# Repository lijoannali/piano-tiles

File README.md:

# Piano Tiles 
A WS2812B LED array game written with "bare metal" C for the MSPM0G3507 for your simple entertainment needs...

## Demo Video

# Full-Length Project Presentation
[Link to Video](https://www.youtube.com/watch?v=sYHI2Lu6KRk)

# Team Members
- Cindy Nguyen
- Maha Razzaq
- Joanna Li
- Ivana Zak
  
# Project Report
[Link to Report](/report.pdf)

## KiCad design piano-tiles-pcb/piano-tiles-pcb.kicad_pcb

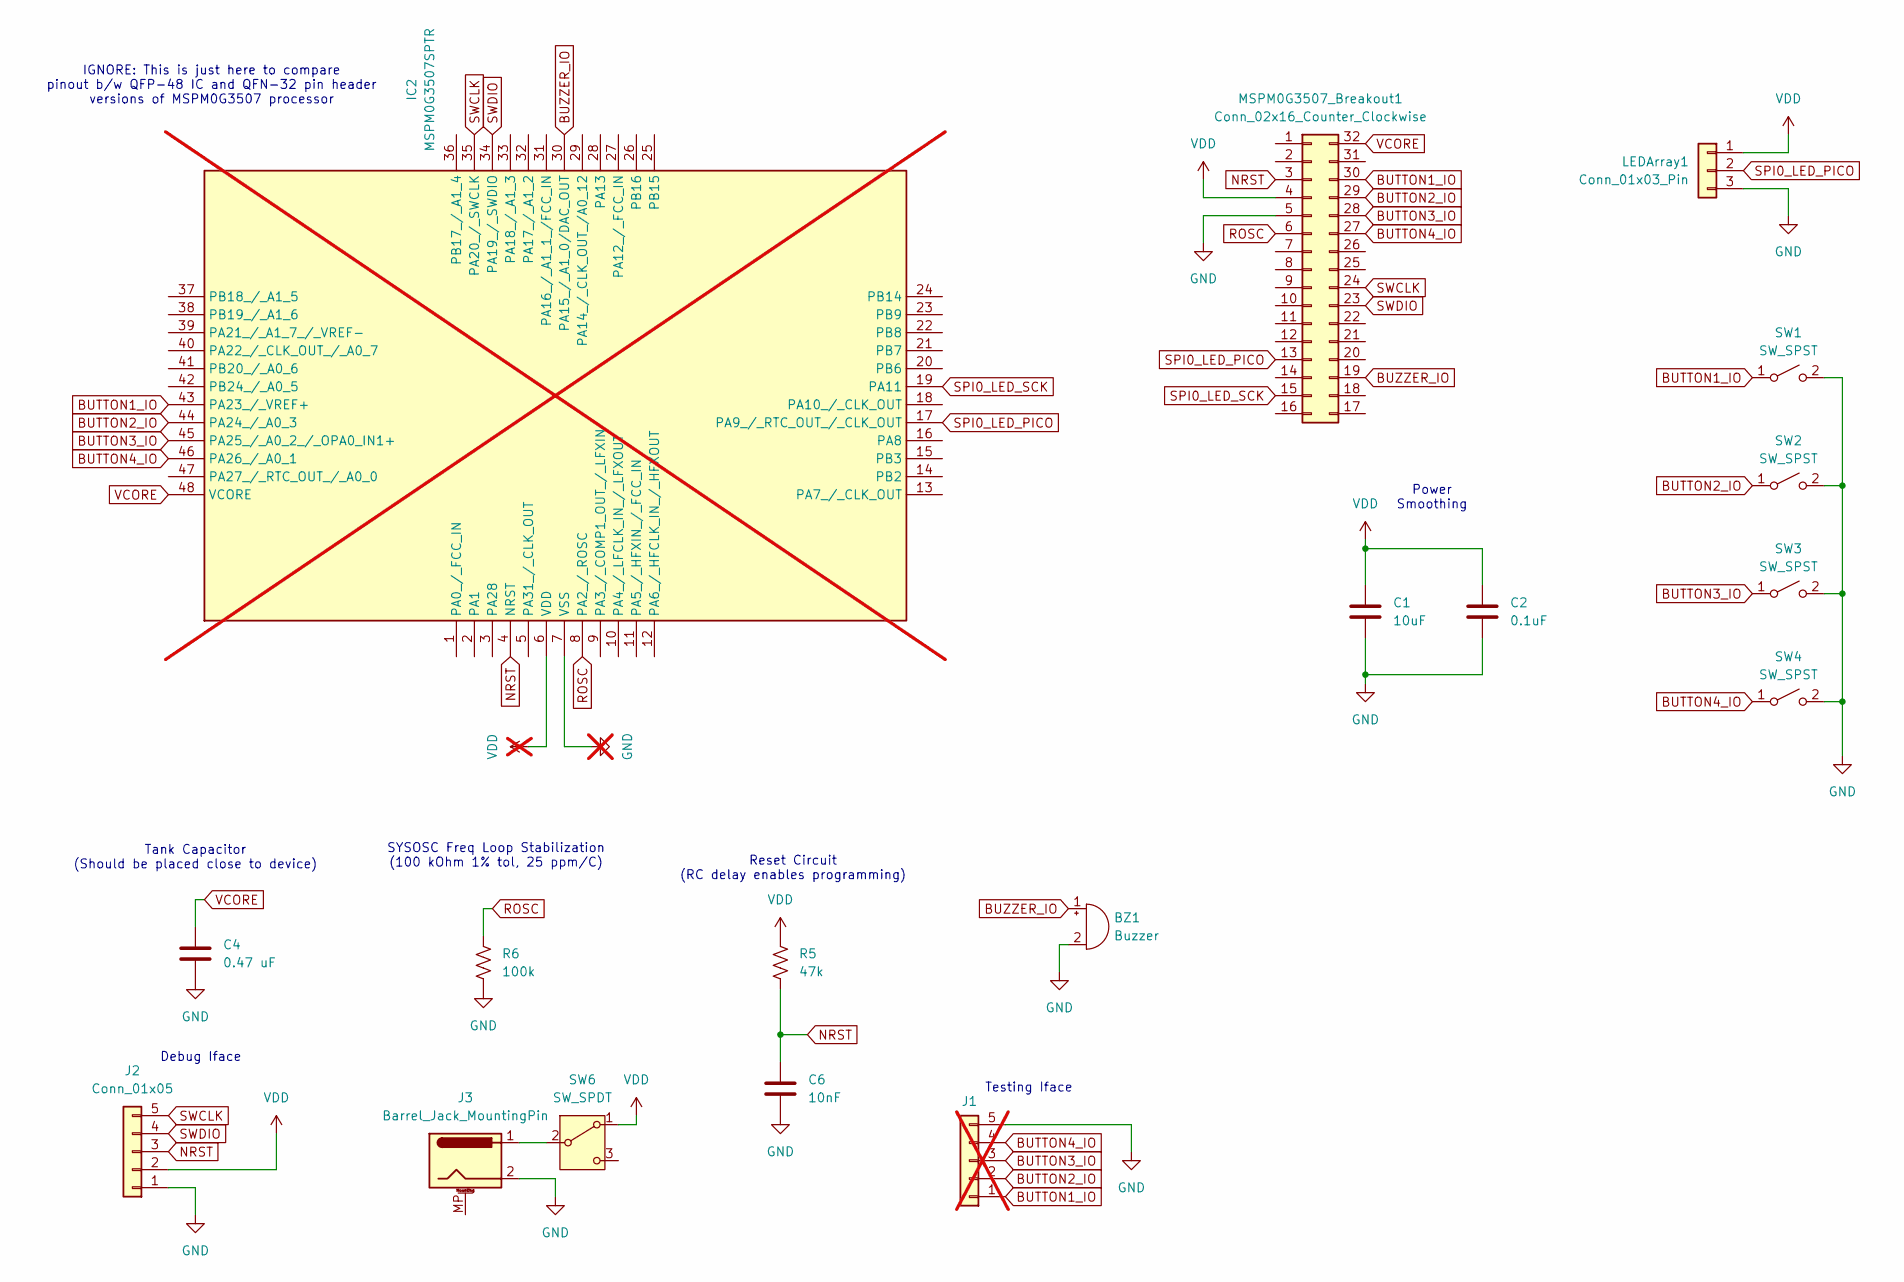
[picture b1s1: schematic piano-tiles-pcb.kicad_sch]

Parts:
BZ1: Buzzer; Buzzer_Murata_PKLCS1212E; LCSC Part # C113159
C1: 10uF; C_1206_3216Metric_Pad1.33x1.80mm_HandSolder
C2: 0.1uF; C_1206_3216Metric_Pad1.33x1.80mm_HandSolder
C4: 0.47 uF; C_1206_3216Metric_Pad1.33x1.80mm_HandSolder; LCSC Part # C13967
C6: 10nF; C_1206_3216Metric_Pad1.33x1.80mm_HandSolder; LCSC Part # C15195
IC2: MSPM0G3507SPTR; QFP50P900X900X160-48N; Mouser Part Number 595-MSPM0G3507SPTR; not fitted
J1: Conn_01x05; PinHeader_1x05_P2.54mm_Horizontal; not fitted
J2: Conn_01x05; PinHeader_1x05_P2.54mm_Horizontal; LCSC Part # C492413
J3: Barrel_Jack_MountingPin; BarrelJack_CUI_PJ-063AH_Horizontal
LEDArray1: Conn_01x03_Pin; PinHeader_1x03_P2.54mm_Horizontal
MSPM0G3507_Breakout1: Conn_02x16_Counter_Clockwise; QFN32Breakout-PinHeader_2x16_P2.54mm_Vertical
R5: 47k; R_1206_3216Metric_Pad1.30x1.75mm_HandSolder; LCSC Part # C105579
R6: 100k; R_1206_3216Metric_Pad1.30x1.75mm_HandSolder; LCSC Part # C60491
SW1, SW2, SW3, SW4: SW_SPST; SW_PUSH_6mm_H5mm
SW6: SW_SPDT; SW_EG1270; MPN C20611678; LCSC Part # C20611678

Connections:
BUTTON1_IO: IC2.43 (PA23_/_VREF+), J1.1, MSPM0G3507_Breakout1.30, SW1.1 (A)
BUTTON2_IO: IC2.44 (PA24_/_A0_3), J1.2, MSPM0G3507_Breakout1.29, SW2.1 (A)
BUTTON3_IO: IC2.45 (PA25_/_A0_2_/_OPA0_IN1+), J1.3, MSPM0G3507_Breakout1.28, SW3.1 (A)
BUTTON4_IO: IC2.46 (PA26_/_A0_1), J1.4, MSPM0G3507_Breakout1.27, SW4.1 (A)
BUZZER_IO: BZ1.1 (+), IC2.30 (PA15_/_A1_0/DAC_OUT), MSPM0G3507_Breakout1.19
GND: BZ1.2 (-), C1.2, C2.2, C4.2, C6.2, IC2.7 (VSS), J1.5, J2.1, J3.2, LEDArray1.3, MSPM0G3507_Breakout1.5, R6.1, SW1.2 (B), SW2.2 (B), SW3.2 (B), SW4.2 (B)
NRST: C6.1, IC2.4 (NRST), J2.3, MSPM0G3507_Breakout1.3, R5.1
unnamed: J3.1, SW6.2 (B)
ROSC: IC2.8 (PA2_/_ROSC), MSPM0G3507_Breakout1.6, R6.2
SPI0_LED_PICO: IC2.17 (PA9_/_RTC_OUT_/_CLK_OUT), LEDArray1.2, MSPM0G3507_Breakout1.13
SPI0_LED_SCK: IC2.19 (PA11), MSPM0G3507_Breakout1.15
SWCLK: IC2.35 (PA20_/_SWCLK), J2.5, MSPM0G3507_Breakout1.24
SWDIO: IC2.34 (PA19_/_SWDIO), J2.4, MSPM0G3507_Breakout1.23
VCORE: C4.1, IC2.48 (VCORE), MSPM0G3507_Breakout1.32
VDD: C1.1, C2.1, IC2.6 (VDD), J2.2, LEDArray1.1, MSPM0G3507_Breakout1.4, R5.2, SW6.1 (A)

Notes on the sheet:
Debug Iface
IGNORE: This is just here to compare pinout b/w QFP-48 IC and QFN-32 pin header versions of MSPM0G3507 processor
Reset Circuit (RC delay enables programming)
Power Smoothing
SYSOSC Freq Loop Stabilization (100 kOhm 1% tol, 25 ppm/C)
Testing Iface
Tank Capacitor (Should be placed close to device)

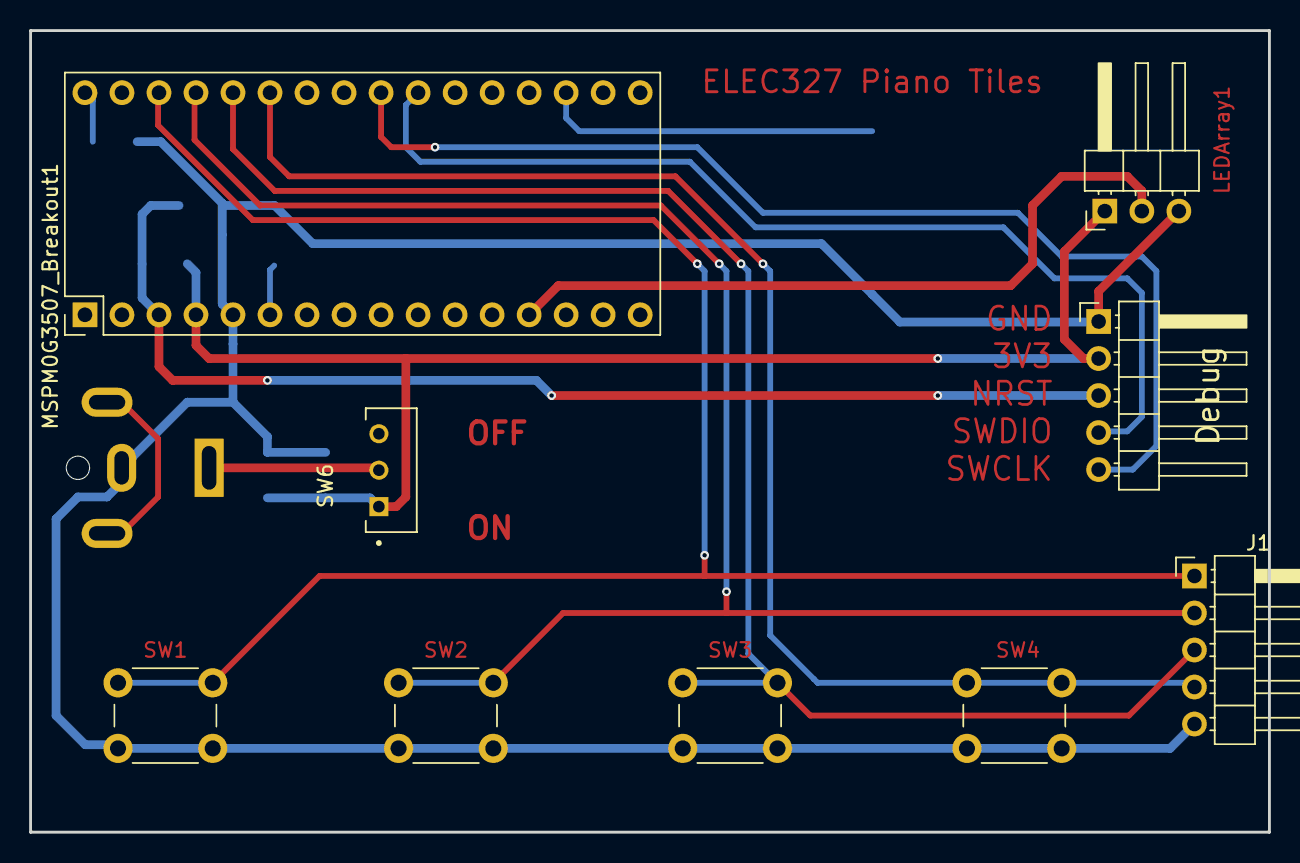
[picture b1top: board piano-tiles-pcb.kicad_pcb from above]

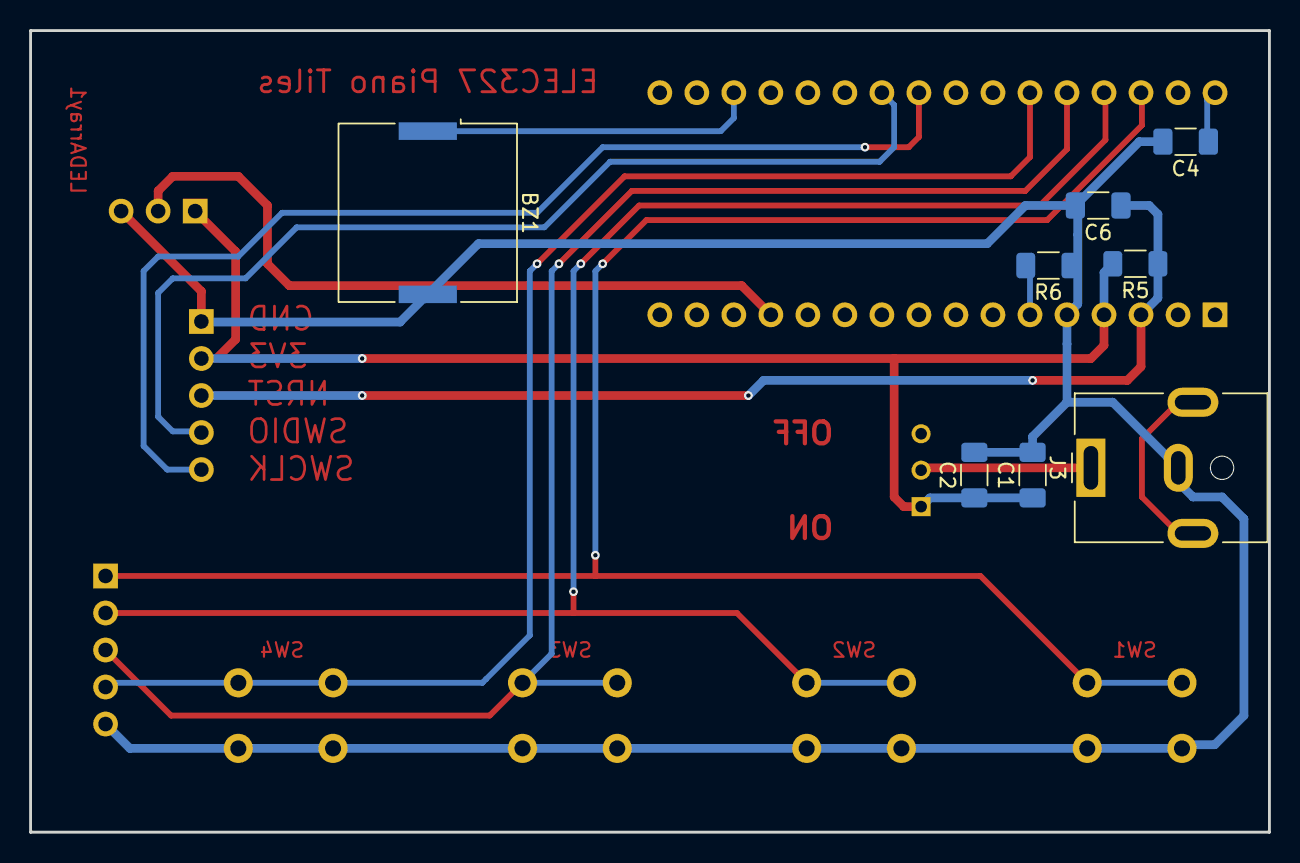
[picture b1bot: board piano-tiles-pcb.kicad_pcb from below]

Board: 2 copper layers, 85.0 x 55.0 mm, 17 parts (8 on the bottom side), 14 nets.

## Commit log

2026-04-04 Upload basic SPI setup to adapt to LED array
2026-04-08 Verify we can turn on GPIOB and PB8 for GPIO. Next step, turn on SPI on PB8
2026-04-08 We successfully sent SPI from PA9 PICO to the array. it did not light up red as intended, oops
2026-04-08 Fixed 0s from 000000 to the 100 zeros to match protocol of Ws2822b
2026-04-12 PCB draft v1
2026-04-13 Adding buttons code
2026-04-15 Implement frame buffer for writing a row to LED array
2026-04-16 Add macros for led dimensions and bit packing
2026-04-16 Add blue and green as LED color options
2026-04-16 Implement rectangle drawing function
2026-04-16 Add falling rectangles example
2026-04-16 Fix SPI clock and setup
2026-04-16 Fix led header, remove unused functions
2026-04-17 Add initial selection of 4 GPIO pins for button input
2026-04-17 Add delay files
2026-04-17 Include falling rectangles example in main
2026-04-17 Update main
2026-04-22 Committing
2026-04-24 first order
2026-04-30 Works with 4 falling tile columns
2026-05-02 Display linked image to demo video
2026-05-02 Update vid thumbnail
2026-05-05 Add links to full presentation and report
2026-05-05 Add project report
